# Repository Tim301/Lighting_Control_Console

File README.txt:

# Lighting_Control_Console
An open source lighting control console developed by MASTER's degree students of DREAM course at Valenciennes.
-> https://formations.uphf.fr/cdm/subProgram/FR_RNE_0593279U_PR_SOF-15676/FR_RNE_0593279U_PR_SOF-15679

DMX_Core.ino create DMX512 signals for RS485 chip. // Actually under construction.

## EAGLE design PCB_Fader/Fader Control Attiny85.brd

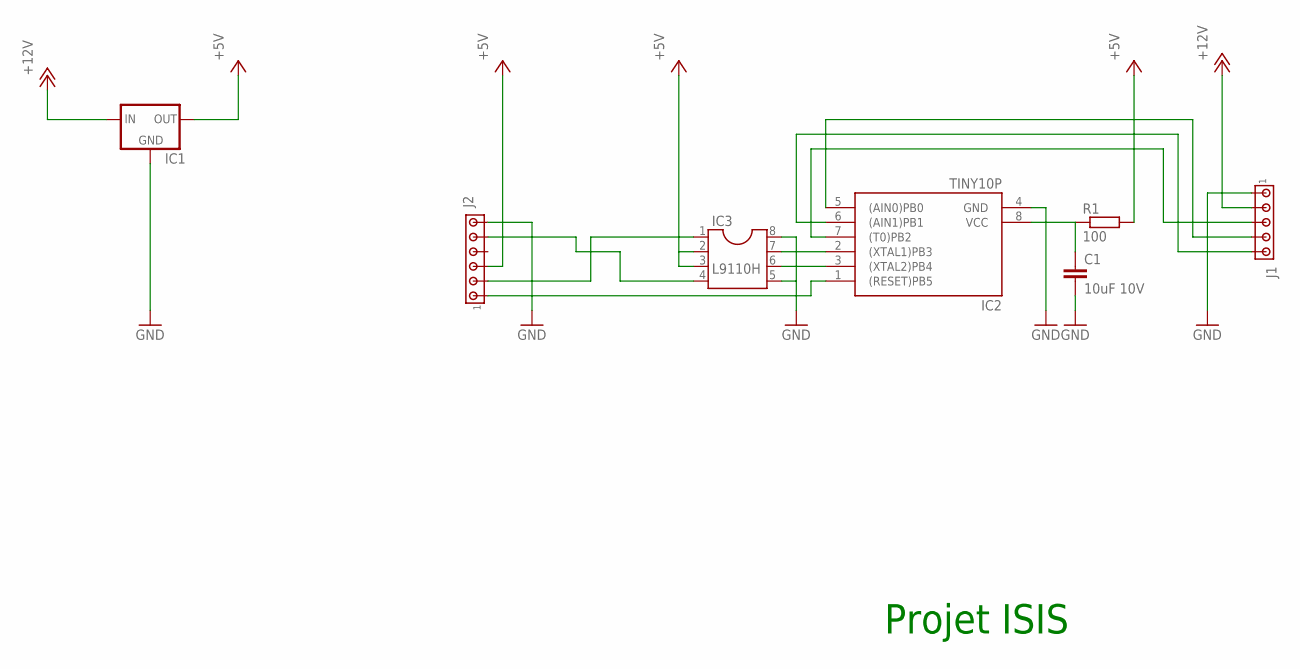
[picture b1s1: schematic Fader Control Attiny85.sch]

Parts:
C1: 10uF 10V; C050-024X044
IC1: 78MXXS
IC2: TINY10P; DIL08
IC3: L9110H; DIL08
J1: MTA05-100; 10X05MTA
J2: MTA06-100; 10X06MTA
R1: 100; 0204/7

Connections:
+5V: IC1.OUT, IC3.2, IC3.3, J2.3, R1.2
+12V: IC1.IN, J1.2
GND: C1.2, IC1.GND, IC2.4 (GND), IC3.5, IC3.8, J1.1, J2.6
unnamed: IC3.1, J2.2
unnamed: IC3.4, J2.5
unnamed: IC2.3 ((XTAL2)PB4), IC3.6
unnamed: IC2.2 ((XTAL1)PB3), IC3.7
unnamed: IC2.1 ((RESET)PB5), J2.1
unnamed: C1.1, IC2.8 (VCC), R1.1
unnamed: IC2.7 ((T0)PB2), J1.3
unnamed: IC2.6 ((AIN1)PB1), J1.5
unnamed: IC2.5 ((AIN0)PB0), J1.4

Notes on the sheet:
Projet ISIS

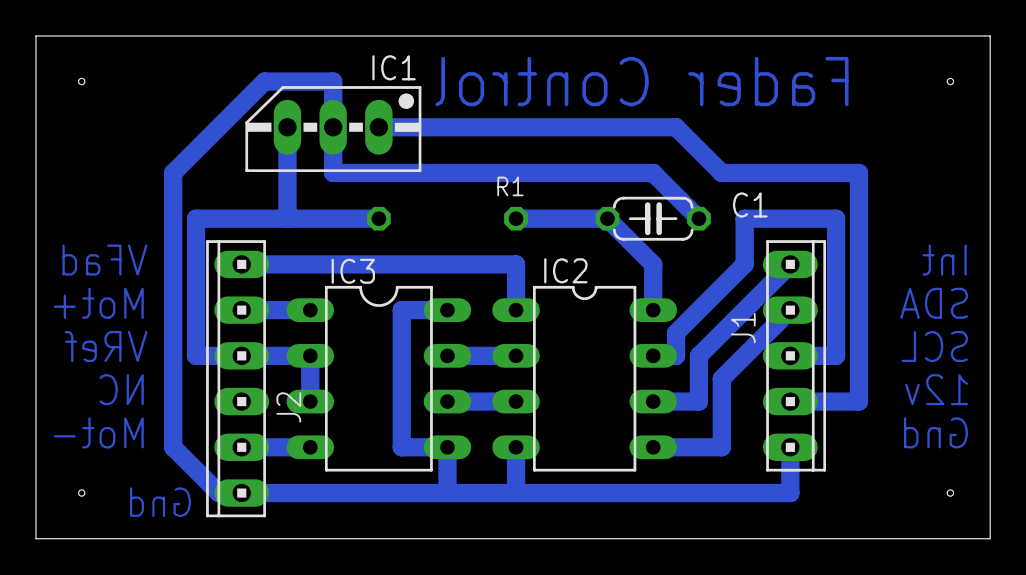
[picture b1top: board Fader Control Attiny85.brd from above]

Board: 2 copper layers, 53.0 x 27.9 mm, 7 parts (1 on the bottom side), 12 nets.

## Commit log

2018-11-28 Rename DMX.ino to DMX_Core_v0.1.ino
2018-12-05 Rename Attiny_Fader.ino to Attiny_Fader_v0.1.ino
2019-02-12 I2C libraries and source code
    These I2C libraires allow the RPI to communicate with an LCD I2C screen
2019-02-16 Add files via upload
    Simple benchmark for ADC MCP3008
2019-02-17 Delete Benchmark_ADC.py
    Moved to /Tools
2019-02-26 Create dmx.py
    First test dmx generator for raspberry pi.
2019-02-26 Update and rename dmx.py to DMX.py
    Personal DMX library for Raspberry Pi using Python.
    v1.0 - Works
2019-03-04 Add files via upload
    This program display a fader's value converted with an ADC on a little OLED screen. There is a hudge latency problem. If someone fix this lattency, let me know.
2019-04-14 ATtiny and rpi communication
    Sending ADC's ATtiny values to the Rpi with I2C protocol
2019-04-30 Add files via upload
    DMX signal generator for pi.
2019-05-01 Update DMX_Sender.py
    include master fonction
2019-05-06 Add files via upload
    PCB files for fader control with attiny.
2019-05-23 Add files via upload
    Workfull version of Attiny fader position
2019-05-23 Rename Attiny_Core_28.ino to Attiny_Core.ino
2019-05-23 Add files via upload
    DMX+i2c fader
